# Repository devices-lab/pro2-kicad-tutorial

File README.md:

# KiCad PCB design walk-through

In this tutorial, your task is to complete the design of the solder:bit Gamepad! The design is missing several buttons, LEDs, and passive components (resistors and capacitors). Help us finish the design before we send it off to the PCB manufacturer!

The solder:bit Gamepad is a kit for learning to solder with surface-mount (SMT) components. You can find out more about the solder:bit Gamepad in [this GitHub repository](https://github.com/devices-lab/solderbit-gamepad).

## Getting started

1. Download or clone this repository.
2. Inside the [kicad](./kicad/) folder, open `solderbit-gamepad.kicad_pro`.
3. Begin with the Schematic Editor 

   Add all the missing symbols and wire them up. For the list of missing parts, see the [section below](#what-components-are-missing).

> [!TIP]
> The grey boxes in the schematic hint at which components are missing and need adding.

4. Next, transition over to the PCB Editor 

   Bring in your changes from the schematic, place component footprints, and route them with traces.

> [!TIP]
> The placeholders on the `User.Drawings` layer to help you with positioning the footprints in the correct locations.

You can preview your PCB in 3D by pressing `Alt+3` (or `Option+3` on a Mac), or by going to `View` &#8594; `3D Viewer` in the PCB Editor.

5. Generate fabrication files for manufacturing and export some nice renders of your device!

> [!NOTE]
> The steps above are just to give you an idea of the plan for the tutorial session. Detailed design steps will be demonstrated live during the session. If you have any questions, please ask the presenter or one of the assistants in the room!

> [!TIP]
> Our aim is to introduce you to PCB design, so don't worry about finishing everything perfectly. Feel free to reuse any part of this project to explore further, and if you'd like to keep learning, there are plenty of great tutorials and videos online to take you further.

## What components are missing?

As previously mentioned, your task is to add in the missing components. That includes the following:

| Component name/value | How many do I need to add? | Schematic symbol                                                                                                       | 3D preview                                                                                                |
| -------------------- | -------------------------- | ---------------------------------------------------------------------------------------------------------------------- | --------------------------------------------------------------------------------------------------------- |
| Tactile switch       | 5                          |                   |                   |
| 90° tactile switch   | 1                          |  |  |
| 100 kΩ resistor      | 6                          |                         |                         |
| WS2812B (NeoPixel)   | 4                          |                           |                           |
| 1 µF capacitor       | 4                          |                       |                       |

In the session we will show you where to find the correct schematic symbols and footprints, and which ones to use from our `SolderbitGamepad` library (already linked to your this project).

## Useful resources

- Check out [KiCad documentation](https://docs.kicad.org/) to get started
- Check out the [reference](./reference/) folder in this repository, it contains datasheets for some of the components you will be working with
- Check out the full design in the [solder:bit Gamepad GitHub repository](https://github.com/devices-lab/solderbit-gamepad)

## Credits

Special thanks to [Dr John Vidler](https://github.com/JohnVidler), everyone at the [Devices Lab](https://www.devices-lab.org/), and to [pro² network+](https://prosquared.org/) for organising the summer schools. Also thank you to all the summer school delegates who discovered a new skill in PCB design.

## License

This project is licensed under the GNU General Public License (GPL), version 3. This license allows you to use, modify, and redistribute the solder:bit Gamepad and any derivative works, but all such derivatives must also be licensed under the GPL.

The GPL ensures that all modifications and improvements to the solder:bit Gamepad remain free and open for the public benefit. By using this project, you agree to abide by its terms and conditions.

For more details on the license, please see the [LICENSE](/LICENSE) file included in this repository.

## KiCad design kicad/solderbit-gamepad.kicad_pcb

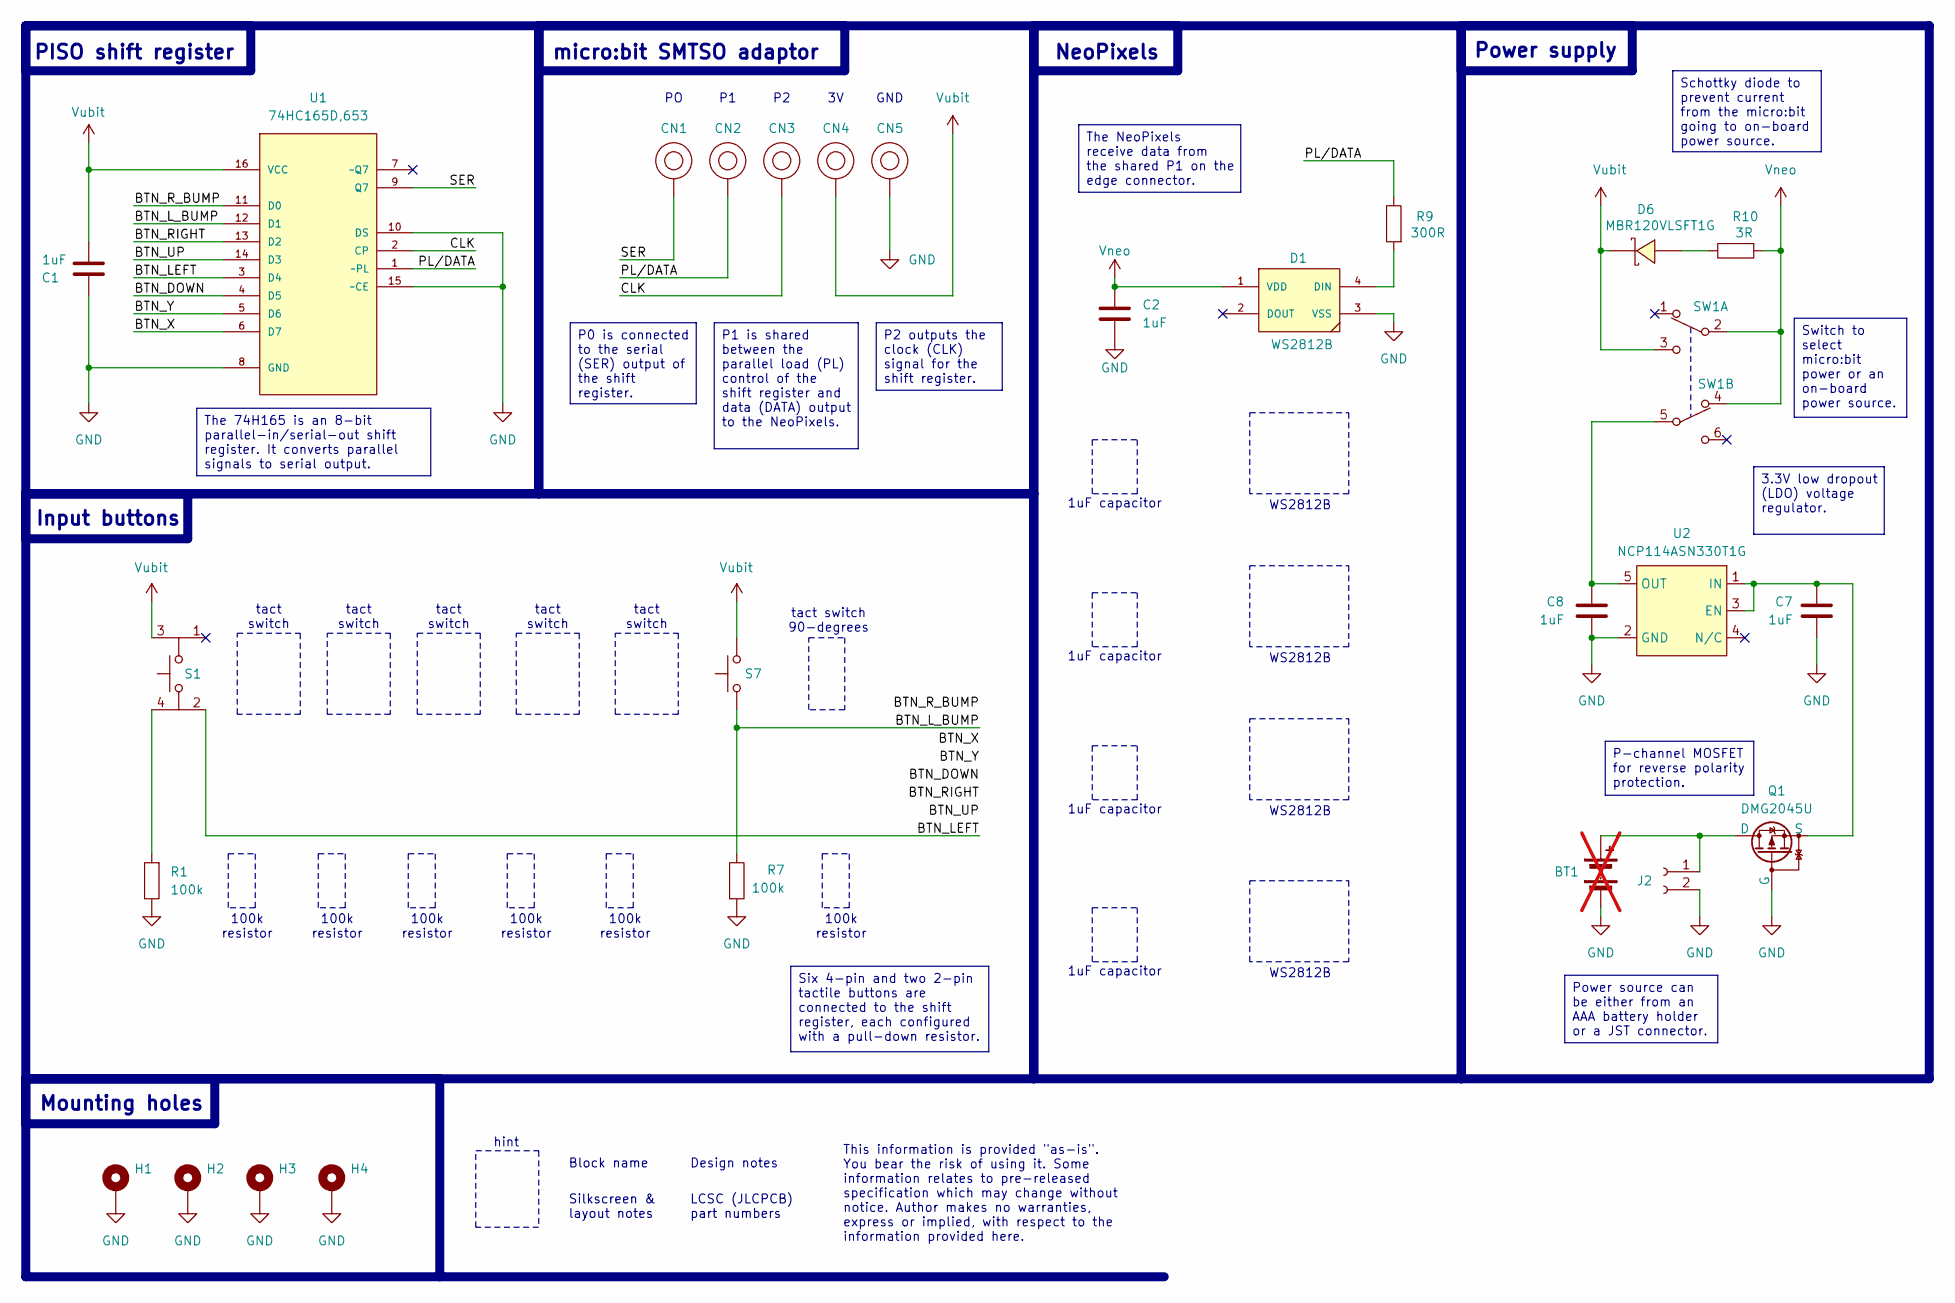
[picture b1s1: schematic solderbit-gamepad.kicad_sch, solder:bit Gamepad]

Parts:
BT1: BH-AAA-B5AA001; Battery_Holder; Part type Extended; LCSC Part C964881; not fitted
C1, C2, C7, C8: 1uF; 1206_Capacitor; Part type Basic; LCSC Part C1848
CN1, CN2, CN3, CN4, CN5: SMTSOM310BTR; Part type Extended; LCSC Part C2915635
D1: WS2812B; NeoPixel_WS2812B; Part type Extended; LCSC Part C2843785
D6: MBR120VLSFT1G; SOD-123FL; Part type Extended; LCSC Part C223608
H1, H2, H3, H4: MountingHole_Pad
J2: S2B-PH-SM4-TB(LF)(SN); JST_PH_S2B-PH-SM4-TB; Part type Extended; LCSC Part C295747
Q1: DMG2045U; TSOT-23; Part type Extended; LCSC Part C459541
R1, R7: 100k; 1206_Resistor; Part type Basic; LCSC Part C17900
R9: 300R; 1206_Resistor; Part type Basic; LCSC Part C17887
R10: 3R; 1206_Resistor; Part type Extended; LCSC Part C17939
S1: KH-6X6X6H-STM; Tactile_Switch; Part type Extended; LCSC Part C2837532
S7: TS-1037-A4B3-D2; Tactile_Switch_Left_90_Degrees; Part type Extended; LCSC Part C499324
SW1: MST22D18G2 125; Sliding_Switch_DPDT; Part type Extended; LCSC Part C2906280
U1: 74HC165D,653; Shift_Register_74HC165D; Part type Extended promotional; LCSC Part C5613
U2: NCP114ASN330T1G; TSOP-5; Part type Extended; LCSC Part C457666

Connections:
/BTN_DOWN: U1.4 (D5)
/BTN_LEFT: S1.2, U1.3 (D4)
/BTN_L_BUMP: R7.2, S7.2, U1.12 (D1)
/BTN_RIGHT: U1.13 (D2)
/BTN_R_BUMP: U1.11 (D0)
/BTN_UP: U1.14 (D3)
/BTN_X: U1.6 (D7)
/BTN_Y: U1.5 (D6)
/CLK: CN3.1, U1.2 (CP)
/PL/DATA: CN2.1, R9.2, U1.1 (~PL)
/SER: CN1.1, U1.9 (Q7)
GND: BT1.2 (-), C1.1, C2.2, C7.2, C8.2, CN5.1, D1.3 (VSS), H1.1 (1_1), H2.1 (1_1), H3.1 (1_1), H4.1 (1_1), J2.2, Q1.1 (G), R1.2, R7.1, U1.8 (GND), U1.10 (DS), U1.15 (~CE), U2.2 (GND)
unnamed: BT1.1 (+), J2.1, Q1.3 (D)
unnamed: D1.4 (DIN), R9.1
unnamed: D6.2, R10.2
unnamed: C7.1, Q1.2 (S), U2.1 (IN), U2.3 (EN)
unnamed: R1.1, S1.4
unnamed: C8.1, SW1.5 (B), U2.5 (OUT)
Vneo: C2.1, D1.1 (VDD), R10.1, SW1.2 (B), SW1.4 (A)
Vubit: C1.2, CN4.1, D6.1, S1.3, S7.1, SW1.3 (C), U1.16 (VCC)

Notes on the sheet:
1uF capacitor
WS2812B
tact switch
Mounting holes
100k resistor
hint
PISO shift register
Power supply
tact switch 90-degrees
Input buttons
micro:bit SMTSO adaptor
NeoPixels
GND
Design notes
Six 4-pin and two 2-pin tactile buttons are connected to the shift register, each configured with a pull-down resistor.
P2 outputs the clock (CLK) signal for the shift register.
P-channel MOSFET for reverse polarity protection.
Schottky diode to prevent current from the micro:bit going to on-board power source.
Silkscreen & layout notes
P0 is connected to the serial (SER) output of the shift register.
The NeoPixels receive data from the shared P1 on the edge connector.
3.3V low dropout (LDO) voltage regulator.
Block name
Switch to select micro:bit power or an on-board power source.
LCSC (JLCPCB) part numbers
P1 is shared between the parallel load (PL) control of the shift register and data (DATA) output to the NeoPixels.
This information is provided "as-is". You bear the risk of using it. Some information relates to pre-released specification which may change without notice. Author makes no warranties, express or implied, with respect to the information provided here.
The 74H165 is an 8-bit parallel-in/serial-out shift register. It converts parallel signals to serial output.
Power source can be either from an AAA battery holder or a JST connector.

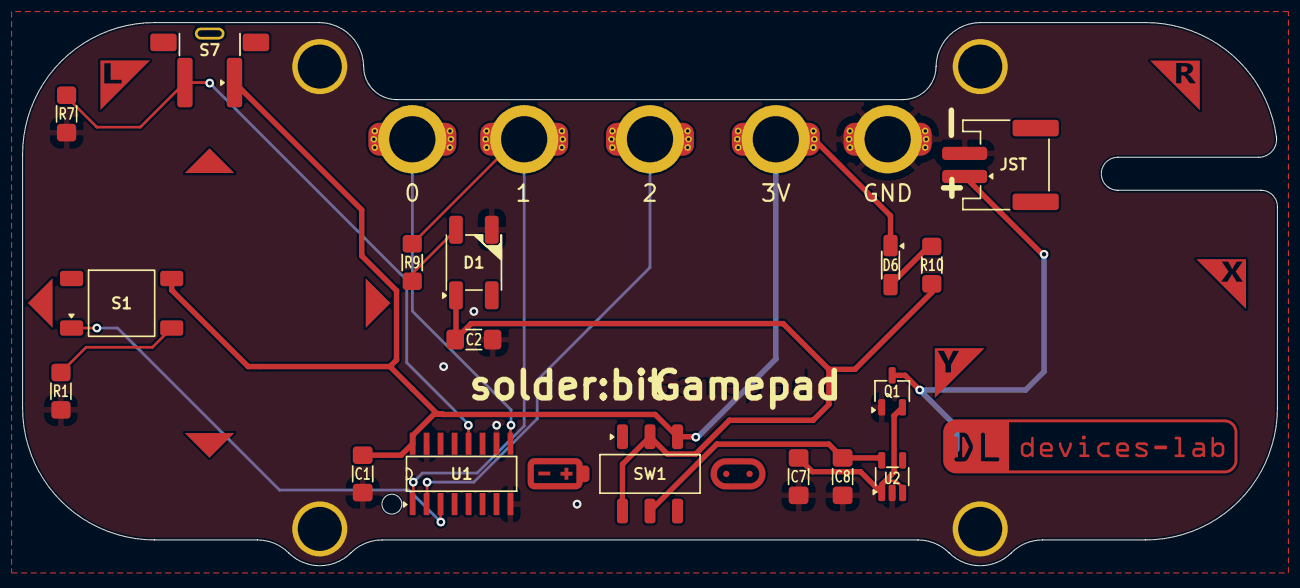
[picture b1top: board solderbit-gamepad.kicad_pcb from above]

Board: 2 copper layers, 114.0 x 49.3 mm, 35 parts (1 on the bottom side), 14 nets.

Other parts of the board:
Ref**: Val**; Button_Label_Y
Ref**#2, Ref**#3, Ref**#4, Ref**#8: Val**; Button_Label_Arrow
Ref**#5: Val**; Button_Label_L
Ref**#6: Val**; Button_Label_X
Ref**#7: Val**; Button_Label_R

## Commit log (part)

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2025-07-11 Added all new project files and updated README.md for 2025 workshop
2025-07-11 .DS_Store removed
2025-07-15 New joystick component and removed some library links
2025-07-15 Removed the microbit and screws 3D models
